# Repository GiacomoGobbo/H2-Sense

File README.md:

# H2Sense Boards

KiCad hardware projects for a battery-powered hydrogen (H2) sensor node.
 
## SensorNode
 
The sensor node detects hydrogen using a surface acoustic wave (SAW) resonator as the sensing element. The resonator sets the frequency of an oscillator at about 110 MHz, and exposure to hydrogen shifts that frequency. The amount of shift indicates the H2 concentration.
 
To make the shift easy to measure, the 110 MHz signal is mixed with a stable commercial 120 MHz reference. The resulting beat frequency, around 10 MHz, is filtered and squared up by a comparator. Its frequency can then be counted digitally, and any change in it follows the change in the sensor frequency.
 
Because the measurement relies on small frequency shifts, the stability and spectral purity of both oscillators are central to the design. This drives most of the choices on both boards: low-noise post-regulation, separate filtered supply branches, and keeping the switching converters off the RF board.

### Architecture

```
Battery ──► PowerBoard ──► 3.3 V / 5 V / −0.55 V ──► RF board

RF board:
  Pierce oscillator + SAW (~110 MHz) ──► IF port ┐
                                                 ├─ Mixer ──► Filter (~10 MHz) ──► Comparator ──► SMA_out
  Commercial 120 MHz oscillator ──────► LO port  ┘
```

### Repository structure

```
PCBprojects/
├── .gitignore
├── README.md
└── SensorNode/
    └── PowerBoard/      Power supply board (KiCad project)
```

The RF board will be added in its own subfolder of `SensorNode/`.

---

## PowerBoard

A separate power supply board that keeps the switching converters off the RF board. It is a test board: it provides footprints for two alternative buck converters, low-noise post-regulation with LDOs, a negative gate bias line, and adjustable test loads.

### Block diagram

```
J1 Battery (Vin)
   │
   ├──► U3  Dual buck module (Vin ≤ 6 V)   ┐   only one of the two
   │                                       ├── is populated
   └──► U6  LTC3607 dual buck (4.5–15 V)   ┘
              │
              ├── Buck_3V5 (~3.47 V) ──► U1 LDO 3.3 V ──► 3V3 ──► J4
              │                                           │
              │                                           └──► U4 TC7660 ──► −3V3
              │                                                               │
              │                         3V3 + −3V3 ──► U5 OPA191 ──► −0.55 V ─┴─► J2 (Vg)
              │
              └── Buck_5V3 (~5.31 V) ──► U2 LDO 5 V ──► 5V ──► J3, J4
```

### Input

| Parameter | Value |
|---|---|
| Connector | J1, 2-pin battery connector (XT30) |
| Input capacitor | C1, 22 µF |
| Input range | Up to 6 V with U3, 4.5–15 V with U6 |

A 2S Li-ion battery (6.0–8.4 V) requires U6. U3 can only be used with an input supply of about 5.5–6 V, since its 5.3 V output needs some headroom.

### Buck converters (populate only one)

U3 and U6 drive the same `Buck_3V5` and `Buck_5V3` nets. **Only one of them must be mounted.**

**U3: dual buck module (input up to 6 V)**

| Output | Feedback divider | Output voltage (VFB = 0.608 V) |
|---|---|---|
| Buck_3V5 (OUT1) | R4 = 100 kΩ, R5 = 21.3 kΩ | ≈ 3.46 V |
| Buck_5V3 (OUT2) | R3 = 100 kΩ, R6 = 13 kΩ | ≈ 5.28 V |

EN1 and EN2 are pulled up to Vin through R1 and R2 (100 kΩ). Output capacitors: C2, C3 (22 µF).

**U6: LTC3607 dual 600 mA synchronous buck (4.5–15 V)**

| Output | Inductor | Feedback divider | Output voltage (VFB = 0.6 V) |
|---|---|---|---|
| Buck_5V3 (SW1) | L1 = 4.7 µH | R23 = 1.82 MΩ, R21 = 232 kΩ, C13 = 22 pF | ≈ 5.31 V |
| Buck_3V5 (SW2) | L2 = 4.7 µH | R24 = 1.11 MΩ, R22 = 232 kΩ, C14 = 22 pF | ≈ 3.47 V |

- Output capacitors: C11, C12 (10 µF).
- RUN1 and RUN2 are tied to Vin, so both outputs start as soon as the battery is connected.
- PGOOD1 and PGOOD2 are pulled up to their outputs through R19 and R20 (100 kΩ).
- **J5** selects the operating mode on MODE/SYNC: pulse skipping (MODE = 0 V) or Burst Mode (MODE > 1 V). Burst Mode is more efficient at light load, pulse skipping gives a more predictable switching spectrum.

### Post-regulation

| Rail | Regulator | Input | Capacitors |
|---|---|---|---|
| 3V3 | U1, LDO 3.3 V (TLV70233, SOT-23-5) | Buck_3V5 | C6 = 1 µF in, C5 = 1 µF out |
| 5V | U2, LDO 5 V | Buck_5V3 | C7 = 2.2 µF in, C4 = 1 µF out |

The bucks run about 0.2–0.3 V above the LDO outputs, so the LDOs dissipate very little while filtering the switching ripple.

### −0.55 V gate bias line

| Part | Function |
|---|---|
| U4, TC7660 | Inverting charge pump: 3V3 → −3V3 (C8 = 10 µF flying, C9 = 10 µF output, LV pin grounded) |
| R9 + C10 | RC filter (1 kΩ, 1 µF) on the op-amp negative supply |
| U5, OPA191 | Inverting amplifier supplied from 3V3 / −3V3, non-inverting input grounded |
| R7 | Input resistor from 3V3 (100 kΩ) |
| R8 + R16 | Fixed feedback: 16.5 kΩ, giving Vout ≈ −3.3 V × 16.5k / 100k ≈ −0.545 V |
| R12 + R17 | Alternative adjustable feedback: 20 kΩ trimmer (Vishay T93YA), range 0 to about −0.66 V |
| J2 | Output connector (Vg) |

Populate **either** R16 (fixed value) **or** R17 (trimmer) as a 0 Ω jumper.

This line is optional. The SKY65050 datasheet recommends self-biasing instead: a source resistor (27–47 Ω, RF-bypassed) with the gate held at 0 V DC, which removes the negative supply and the need for power sequencing.

If the negative line is used on the RF board:

- the gate voltage must be applied **before** the drain supply and removed **after** it;
- the gate current must stay below 100 µA (absolute maximum).

### Outputs

| Connector | Signals |
|---|---|
| J4 (3-pin header) | 5V, 3V3, GND |
| J3 | 5V |
| J2 | −0.55 V (Vg) |

### Test loads

| Rail | Load | Notes |
|---|---|---|
| 5V | R13 (0 Ω) + R11 (20 kΩ trimmer, rheostat) | Adjustable load to GND |
| 3V3 | R14 (0 Ω) + R10 (20 kΩ trimmer, rheostat) | Adjustable load to GND |
| −0.55 V | R15 (0 Ω) + R18 (232 kΩ) | Fixed load, about 2.4 µA |

The 0 Ω resistors disconnect each test load when not mounted.

### Bill of main components

| Ref | Part | Function |
|---|---|---|
| U1 | TI TLV70233 | 3.3 V LDO |
| U2 | 5 V LDO (TBD) | 5 V LDO |
| U3 | Dual buck module, VFB = 0.608 V (TBD) | Buck for inputs up to 6 V |
| U4 | Microchip TC7660EOA713 | Inverting charge pump |
| U5 | TI OPA191IDR | Gate bias op-amp |
| U6 | ADI LTC3607EMSE#PBF | Dual buck, 4.5–15 V |
| R10, R11, R12 | Vishay T93YA203JT20 | 20 kΩ trimmers |
| J1 | Amass XT30 (PCB version) | Battery connector |

### Known issues / TODO

- [ ] **LTC3607 feedback dividers:** in the current schematic the `Vfb1` / `Vfb2` labels are on the bottom end of R21 / R22, which is not connected to GND. The divider midpoint must go to VFB, and the bottom of R21 / R22 must go to GND. As drawn, the outputs would not regulate correctly.
- [ ] **Gate bias output:** add a series resistor (≥ 27–33 kΩ) between U5 OUT and J2 to limit the gate current and isolate the op-amp from capacitive loads, plus an RC filter at the output.
- [ ] **Test loads:** the 20 kΩ trimmers can be turned down to 0 Ω, shorting the rail. Replace R13 / R14 with fixed resistors (for example 68 Ω on 3V3 and 100 Ω on 5V) to limit the maximum current and the trimmer dissipation.
- [ ] **−0.55 V test load:** R18 = 232 kΩ draws about 2.4 µA. Use about 55 kΩ to emulate the expected 10 µA.
- [ ] **Input protection:** no reverse-polarity protection, fuse or undervoltage cutoff yet. A 2S Li-ion battery needs an undervoltage cutoff around 6.0–6.2 V (for example a divider on the RUN pins of U6, or a BMS).
- [ ] **Switching frequency:** the LTC3607 switches at about 2.25 MHz, and its 5th harmonic (11.25 MHz) is close to the 10 MHz IF. Check the spurs at the IF output with the RF board connected.
- [ ] Choose U2 and U3.

---

## RF board

| Block | Part / notes |
|---|---|
| 110 MHz oscillator | Pierce with SKY65050-372LF pHEMT and SAW resonator |
| LO oscillator | Commercial 120 MHz oscillator |
| Mixer | 110 MHz on the IF port, 120 MHz on the LO port, ~10 MHz output |
| Output filter | Low-pass / band-pass around 10 MHz |
| Comparator | Supplied from 5 V and 3.3 V, output on SMA_out |

> **Note:** the SKY65050-372LF is discontinued. Consider a replacement for future revisions.

### Design notes

- Keep the two oscillators (110 and 120 MHz) physically separated and powered from separately filtered branches to avoid mutual pulling and spurs.
- The FET has gain up to several GHz: add a small series resistor on the gate or a ferrite bead on the drain to prevent parasitic oscillations, and check the spectrum up to a few GHz.
- Use a high-value gate DC return (100 kΩ – 1 MΩ) to avoid lowering the resonator Q.
- Use C0G/NP0 capacitors in the Pierce feedback network.
- Continuous ground plane under the whole RF section, with stitching vias and local decoupling (100 nF + nF) on every IC.

---

## Working on the project

### Requirements

- KiCad (state the version used by the team: files saved with a newer version cannot be opened with an older one)
- Git

### Cloning the repository

```
git clone https://github.com/GiacomoGobbo/PCBprojects.git
```

### Workflow

1. Before starting: `git pull`.
2. Work on the project in KiCad.
3. When done:
   ```
   git add .
   git commit -m "Description of the changes"
   git push
   ```

### Rules

- Do not edit the same `.kicad_sch` or `.kicad_pcb` file at the same time: conflicts in KiCad files are hard to resolve. Split the work by board or by schematic sheet.
- Keep custom symbol, footprint and 3D model libraries inside the project folder, using relative paths (`${KIPRJMOD}`).
- The XT30 footprint is in the official `Connector_AMASS` library. Use the `Conn_01x02` symbol in the schematic.
- Do not create nested Git repositories inside project subfolders.
- The `.gitignore` in the root folder excludes backups, autosaves, caches, lock files, local preferences (`.kicad_prl`) and KiCad's local history (`.history/`).

---

## Authors

- Giacomo Gobbo

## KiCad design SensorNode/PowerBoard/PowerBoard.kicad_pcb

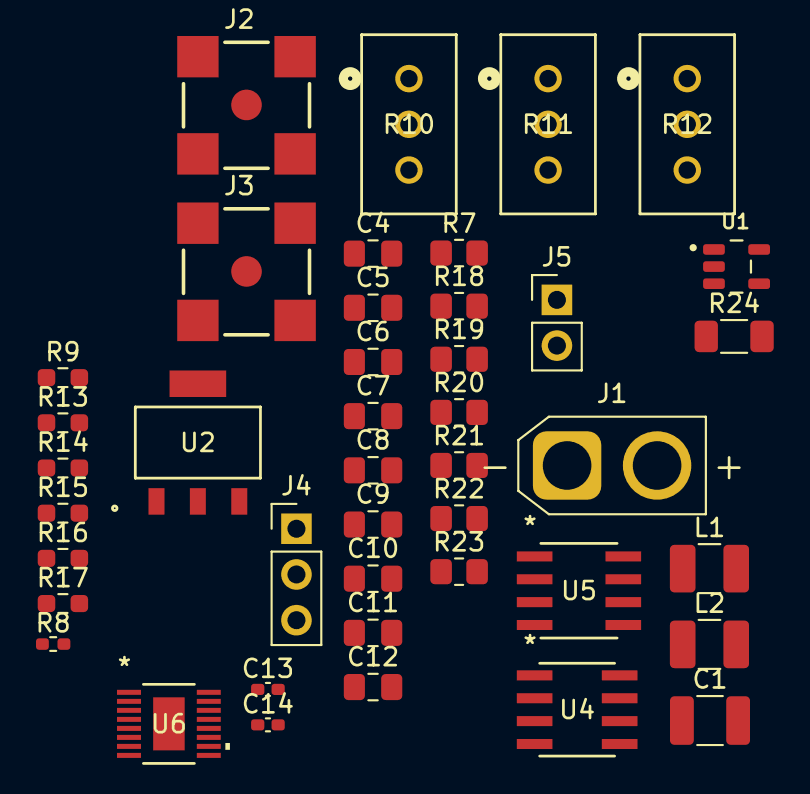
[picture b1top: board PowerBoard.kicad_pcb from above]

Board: 2 copper layers, 42 parts (0 on the bottom side), 26 nets, no tracks yet.

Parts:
C1: 22u; C_1210_3225Metric_Pad1.33x2.70mm_HandSolder
C4, C5, C6, C10: 1u; C_0805_2012Metric_Pad1.18x1.45mm_HandSolder
C7: 2.2u; C_0805_2012Metric_Pad1.18x1.45mm_HandSolder
C8, C9, C11, C12: 10u; C_0805_2012Metric_Pad1.18x1.45mm_HandSolder
C13, C14: 22p; C_0402_1005Metric_Pad0.74x0.62mm_HandSolder
J1: Battery; AMASS_XT30U-M_1x02_P5.0mm_Vertical
J2: Vg; SAMTEC_SMA-J-P-GF-RA-SM1
J3: 5V; SAMTEC_SMA-J-P-GF-RA-SM1
J4: Conn_01x03_Pin; PinHeader_1x03_P2.54mm_Vertical
J5: Mode; PinHeader_1x02_P2.54mm_Vertical
L1, L2: 4.7u; L_1210_3225Metric_Pad1.42x2.65mm_HandSolder
R7, R19, R20: 100k; R_0805_2012Metric_Pad1.20x1.40mm_HandSolder
R8: 16.5k; R_0402_1005Metric_Pad0.72x0.64mm_HandSolder
R9: 1k; R_0603_1608Metric_Pad0.98x0.95mm_HandSolder
R10, R11, R12: T93YA203JT20; POT_T93YA_VIS
R13, R14, R15, R16, R17: 0Ω; R_0603_1608Metric_Pad0.98x0.95mm_HandSolder
R18, R21, R22: 232k; R_0805_2012Metric_Pad1.20x1.40mm_HandSolder
R23: 1.82M; R_0805_2012Metric_Pad1.20x1.40mm_HandSolder
R24: 1.11M; R_1206_3216Metric_Pad1.30x1.75mm_HandSolder
U1: LDO 3V3; SOT95P280X145-5N
U2: LDO 5V; SOT-223_3MC_MCH
U4: TC7660EOA713; SOIC8-N_MC_MCH
U5: OPA191IDR; D0008A_TEX
U6: LTC3607EMSE-PBF; MSOP-16_MSE_LIT

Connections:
/3V3: C5.1, J4.2, R7.2, R14.1, U1.5 (OUT), U4.8, U5.7 (V+)
/5V: C4.1, J3.1, J4.3, R13.1, U2.3 (VOUT)
/-0.55V: J2.1, R12.1, R15.1, R16.2, U5.6 (OUT)
/-3V3: C9.1, R9.1, U4.5
/Buck_3V5: C6.1, C12.1, C14.1, L2.1, R20.1, R24.1, U1.1 (IN), U1.3 (EN)
/Buck_5V3: C7.1, C11.1, C13.1, L1.1, R19.1, R23.1, U2.1 (VIN)
/Vfb1: R21.2, U6.13 (VFB1)
/Vfb2: R22.2, U6.12 (VFB2)
/Vin: C1.1, J1.2, U6.1 (SVIN), U6.4 (PVIN1), U6.5 (PVIN2), U6.11 (RUN2), U6.14 (RUN1)
GND: C1.2, C4.2, C5.2, C6.2, C7.2, C9.2, C10.2, C11.2, C12.2, J1.1, J2.2, J2.3, J2.4, J2.5, J3.2, J3.3, J3.4, J3.5, J4.1, J5.1, R10.2, R11.2, R18.1, U1.2 (GND), U2.2 (GND), U4.3, U4.6, U5.3 (+IN), U6.2 (PGND1), U6.7 (PGND2), U6.8 (SGND), U6.10 (SGND), U6.EPAD
unnamed: C8.1, U4.4
unnamed: C8.2, U4.2
unnamed: C13.2, R21.1, R23.2
unnamed: C14.2, R22.1, R24.2
unnamed: J5.2, U6.15 (MODE/SYNC)
unnamed: R10.3, R14.2
unnamed: R11.3, R13.2
unnamed: R12.2, R17.1
unnamed: R15.2, R18.2
unnamed: R8.2, R16.1
unnamed: R7.1, R8.1, R17.2, U5.2 (-IN)
unnamed: C10.1, R9.2, U5.4 (V-)
unnamed: R19.2, U6.16 (PGOOD1)
unnamed: R20.2, U6.9 (PGOOD2)
unnamed: L1.2, U6.3 (SW1)
unnamed: L2.2, U6.6 (SW2)

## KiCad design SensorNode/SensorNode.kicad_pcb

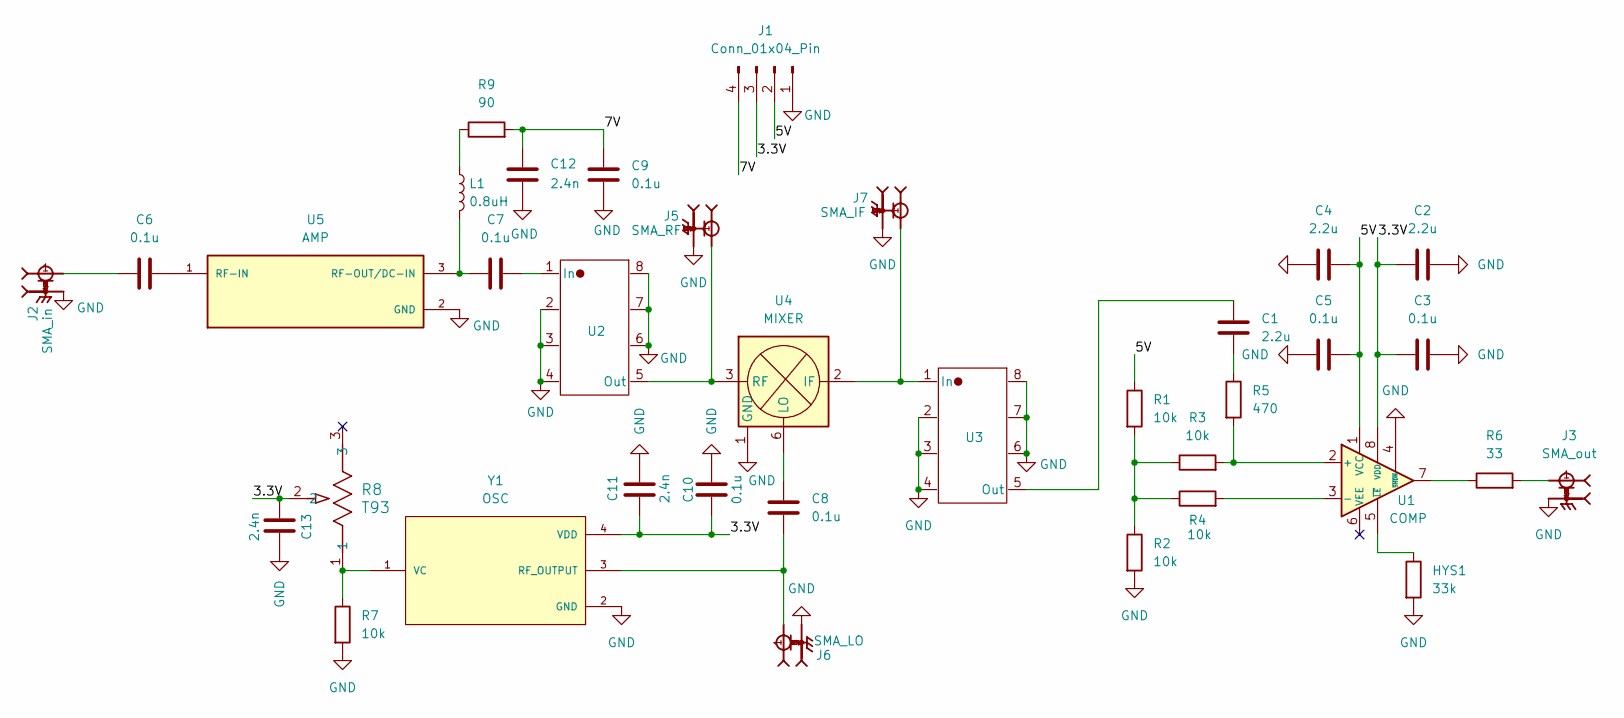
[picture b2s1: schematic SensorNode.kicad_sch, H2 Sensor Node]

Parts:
C1, C2, C4: 2.2u; C_0805_2012Metric_Pad1.18x1.45mm_HandSolder
C3, C5, C6, C7, C8, C9, C10: 0.1u; C_0603_1608Metric_Pad1.08x0.95mm_HandSolder
C11, C12, C13: 2.4n; C_0805_2012Metric_Pad1.18x1.45mm_HandSolder
HYS1: 33k; R_0805_2012Metric_Pad1.20x1.40mm_HandSolder
J1: Conn_01x04_Pin; PinHeader_1x04_P2.54mm_Vertical
J2: SMA_in; SAMTEC_SMA-J-P-GF-RA-SM1; MPN SMA-J-P-GF-RA-SM1
J3: SMA_out; SAMTEC_SMA-J-P-GF-RA-SM1; MPN SMA-J-P-GF-RA-SM1
J5: SMA_RF; SAMTEC_SMA-J-P-GF-RA-SM1; MPN SMA-J-P-GF-RA-SM1
J6: SMA_LO; SAMTEC_SMA-J-P-GF-RA-SM1; MPN SMA-J-P-GF-RA-SM1
J7: SMA_IF; SAMTEC_SMA-J-P-GF-RA-SM1; MPN SMA-J-P-GF-RA-SM1
L1: 0.8uH; L_0805_2012Metric_Pad1.05x1.20mm_HandSolder
R1, R2, R3, R4, R7: 10k; R_0201_0603Metric_Pad0.64x0.40mm_HandSolder
R5: 470; R_0603_1608Metric_Pad0.98x0.95mm_HandSolder
R6: 33; R_1206_3216Metric_Pad1.30x1.75mm_HandSolder
R8: T93; POT_T93YA_VIS
R9: 90; R_0603_1608Metric_Pad0.98x0.95mm_HandSolder
U1: COMP; MSOP-8_3x3mm_P0.65mm
U2, U3: SCLF
U4: MIXER; Mini-Circuits_CD542_LandPatternPL-052
U5: AMP; IC_ERA-6SM_; MPN ERA-6SM+
Y1: OSC; XTAL_ABLNO-V-104.000MHZ-T; MPN ABLNO-V-104.000MHZ

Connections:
/3.3V: C2.1, C3.1, C10.1, C11.2, C13.2, J1.3, R8.2, U1.8 (VDD), Y1.4 (VDD); also elsewhere on the board
/5V: C4.2, C5.2, J1.2, R1.1, U1.1 (VCC); also elsewhere on the board
/7V: C9.2, C12.1, J1.4, R9.2
GND: C2.2, C3.2, C4.1, C5.1, C9.1, C10.2, C11.1, C12.2, C13.1, HYS1.2, J1.1, J2.2, J2.3, J2.4, J2.5, J3.2, J3.3, J3.4, J3.5, J5.2, J5.3, J5.4, J5.5, J6.2, J6.3, J6.4, J6.5, J7.2, J7.3, J7.4, J7.5, R2.2, R7.2, U1.4 (~SHDN), U2.2, U2.3, U2.4, U2.6, U2.7, U2.8, U3.2, U3.3, U3.4, U3.6, U3.7, U3.8, U4.1 (GND), U4.4 (GND), U4.5 (GND), U5.2 (GND), U5.4 (GND), Y1.2 (GND); also elsewhere on the board
unnamed: C1.2, R5.1
unnamed: C6.1, J2.1
unnamed: J3.1, R6.2
unnamed 7: L1.1, R9.1; also elsewhere on the board
unnamed: R1.2, R2.1, R3.1, R4.1
unnamed 9: R6.1, U1.7; also elsewhere on the board
unnamed 10: R3.2, R5.2, U1.2 (+); also elsewhere on the board
unnamed 11: R4.2, U1.3 (-); also elsewhere on the board
unnamed 12: HYS1.1, U1.5 (~LE); also elsewhere on the board
unnamed: C7.2, U2.1 (In)
unnamed: J5.1, U2.5 (Out), U4.3 (RF)
unnamed: J7.1, U3.1 (In), U4.2 (IF)
unnamed: C1.1, U3.5 (Out)
unnamed: C8.2, U4.6 (LO)
unnamed: C6.2, U5.1 (RF-IN)
unnamed 19: C7.1, L1.2, U5.3 (RF-OUT/DC-IN); also elsewhere on the board
unnamed 20: C8.1, J6.1, Y1.3 (RF_OUTPUT); also elsewhere on the board
unnamed 21: R7.1, R8.1, Y1.1 (VC); also elsewhere on the board

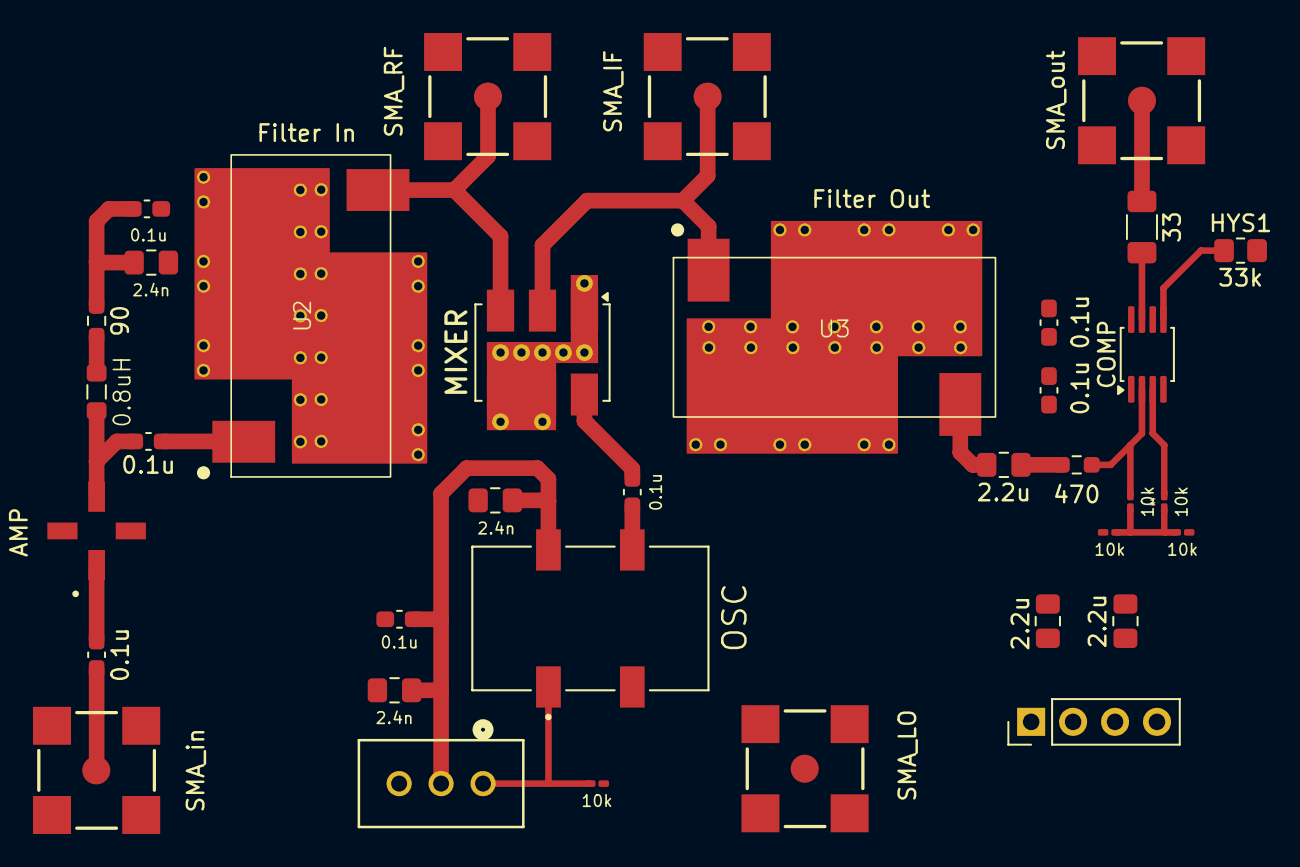
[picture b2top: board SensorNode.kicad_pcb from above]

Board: 2 copper layers, 36 parts (0 on the bottom side), 22 nets.

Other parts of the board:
0.8uH: 0.8uH; L_0805_2012Metric_Pad1.05x1.20mm_HandSolder
COMP: LTC6752xMS8-2; MSOP-8_3x3mm_P0.65mm
OSC: OSC; XTAL_ABLNO-V-104.000MHZ-T

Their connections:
/3.3V: COMP.8 (VDD), OSC.4 (VDD); also elsewhere on the board
/5V: COMP.1 (VCC); also elsewhere on the board
GND: COMP.4 (~SHDN), OSC.2 (GND); also elsewhere on the board
unnamed 7: 0.8uH.1; also elsewhere on the board
unnamed 9: COMP.7; also elsewhere on the board
unnamed 10: COMP.2 (+); also elsewhere on the board
unnamed 11: COMP.3 (-); also elsewhere on the board
unnamed 12: COMP.5 (~LE); also elsewhere on the board
unnamed 19: 0.8uH.2; also elsewhere on the board
unnamed 20: OSC.3 (RF_OUTPUT); also elsewhere on the board
unnamed 21: OSC.1 (VC); also elsewhere on the board
